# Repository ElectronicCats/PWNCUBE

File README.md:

# PWNCUBE - The Vulnerable Satellite Hacking Platform for Learning Through Research

PwnSat is the first open-source, vulnerable-by-design aerospace cybersecurity platform. It bridges the gap between traditional IT security and specialized Space Mission Operations (SMO). Developed over six years of research, PwnSat 2.0 scales from a basic FlatSat to a high-fidelity enterprise environment, designed specifically for advanced offensive and defensive research.

## Project Overview

PwnSat replicates a complete end-to-end space mission ecosystem, allowing researchers to explore vulnerabilities across the entire attack surface:
* **Space Segment:** 1U CubeSat Hardware (OBC, EPS, and Radio).
* **Ground Segment:** Multi-band RF Gateway (LoRa/FSK).
* **C3 Segment:** Native integration with Ball Aerospace COSMOS for enterprise-grade command and control.

## New for v2.0 (Black Hat USA Release)

The 2.0 "Enterprise Edition" introduces critical updates over the initial release:
* **GNSS Attack Module:** Integration of a physical GNSS sensor to simulate signal jamming and positioning spoofing, affecting the satellite's AOCS (Attitude and Orbit Control System).
* **COSMOS C3 Integration:** Support for industry-standard mission control software, replacing custom dashboards with tools used by NASA and commercial space ventures.
* **Ground Station Pivot:** New scenarios demonstrating lateral movement from a compromised MOC backend to the satellite RF uplink.

## Hardware Architecture

The platform is built on custom-designed PCBs (v1.1) optimized for RF integrity and modularity.

### Flight System Components

| Component | Specification |
| :--- | :--- |
| **OBC (Flight Computer)** | ESP32-S3 (Dual-core, hardware encryption support) |
| **Radio Subsystem** | Semtech SX1276/78 (Multi-band LoRa/FSK) |
| **GNSS Module** | Integrated positioning sensor for navigation research |
| **Sensors** | IMU, Thermal, and Simulated Power System (EPS) |

### Hardware Gallery

The following boards represent the core of the PwnSat 1U system:

**1. Main Flight Computer (OBC) & Navigation Board**
This board handles the flight logic, telemetry processing, and the newly integrated GNSS sensor.

**2. RF Communications & Shielding Subsystem**
Dedicated module for handling CCSDS and AX.25 protocol stacks over the physical radio link.

**3. Power Distribution & Modular Bus**
The EPS (Electronic Power System) simulation board, featuring intentional vulnerabilities in power rail management.

## Technical Research Scenarios (SPARTA Mapping)

Each vulnerability in PwnSat is mapped to the **SPARTA (Space Attack Research & Tactics Analysis)** framework to ensure professional-grade research relevance:

### 1. Electronic ASAT (Navigation Spoofing)
Using the new GNSS module, researchers can demonstrate how spoofing signal data tricks the OBC into incorrect positioning calculations, leading to unauthorized attitude maneuvers.

### 2. Space Link Exploitation
* **Uplink Hijacking:** Injecting unauthorized CCSDS frames into the command stream.
* **Telemetry Forgery:** Manipulating AX.25 packets to mask malicious activity on the satellite.

### 3. Ground Segment Lateral Movement
Demonstration of a "Full-Chain" compromise:
* Exploiting a web-based vulnerability in the MOC.
* Pivoting to the COSMOS C3 instance.
* Executing an unauthorized "Kill-Command" through the RF Ground Station.

## Repository Structure

* `/hardware`: KiCad schematics, Gerber files, and Bill of Materials (BOM).
* `/firmware`: ESP32-S3 flight code and radio drivers (PlatformIO).
* `/ground-station`: Dockerized MOC and Ball Aerospace COSMOS configuration files.
* `/docs`: Technical architecture whitepapers and SPARTA mapping guides.

## Disclaimer

PwnSat is intended for educational and ethical research purposes only. Always conduct RF testing within a shielded environment (Faraday cage) to comply with local radio frequency regulations.

## Credits & License

**Developed by:** PWNSAT Team & Electronic Cats
**Research Duration:** 2019 - 2026
**License:** GNU General Public License v3.0

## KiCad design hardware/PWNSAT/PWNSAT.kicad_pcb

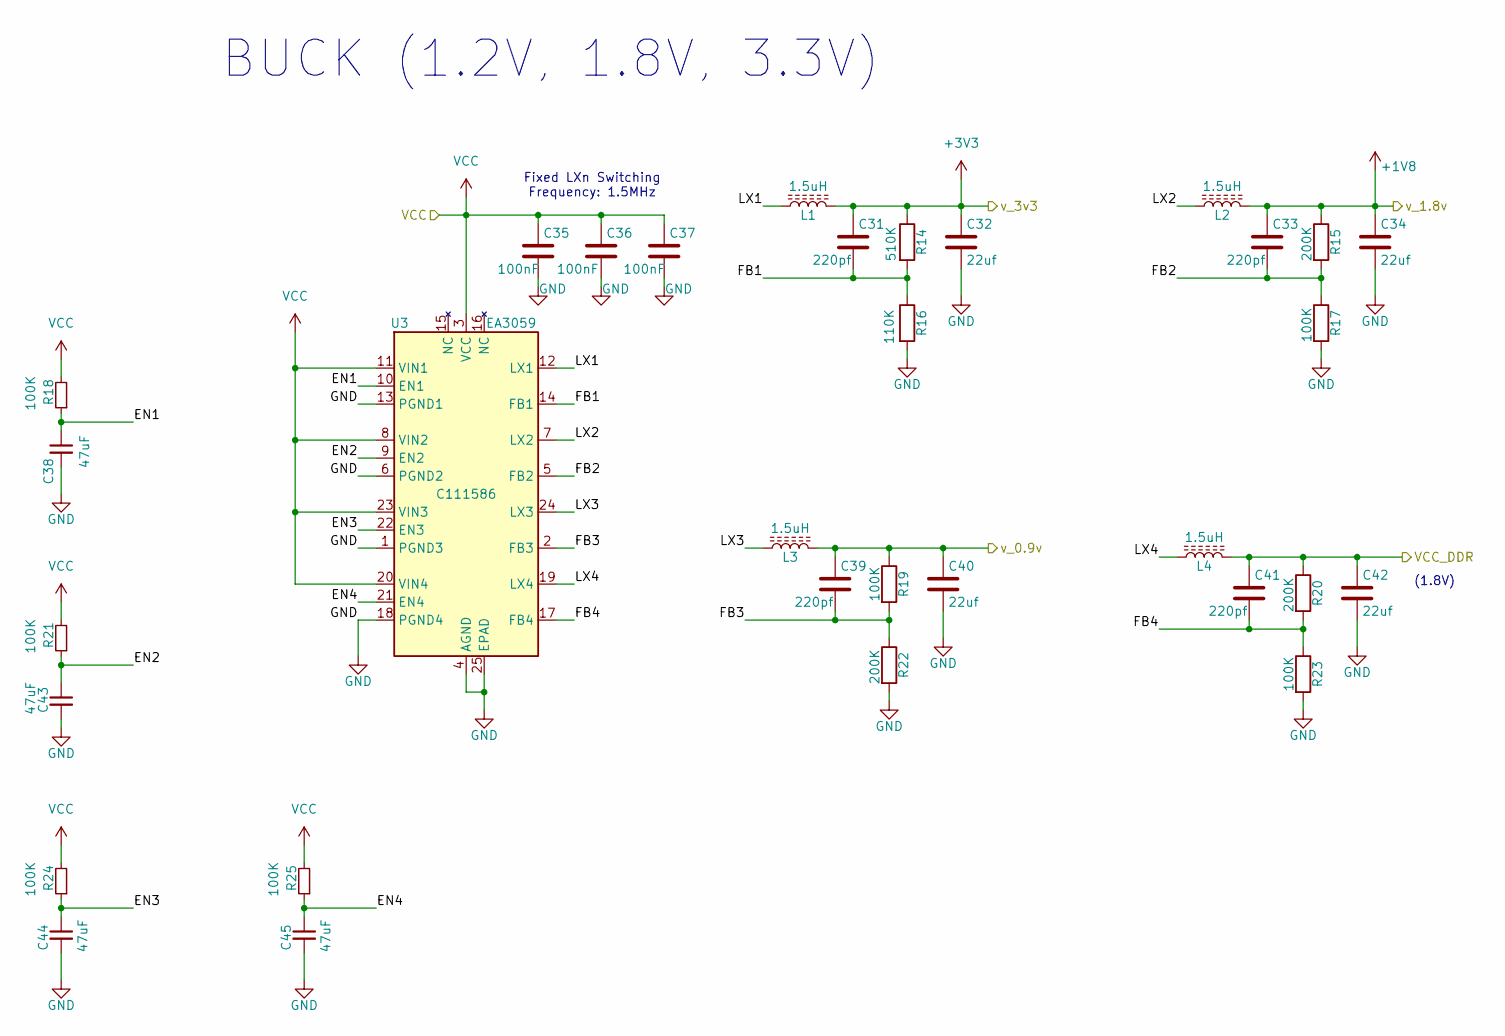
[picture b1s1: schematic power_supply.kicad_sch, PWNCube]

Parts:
C31, C33, C39, C41: 220pf; C_0402_1005Metric_Pad0.74x0.62mm_HandSolder; LCSC# C327000
C32, C34, C40, C42: 22uf; C_0402_1005Metric_Pad0.74x0.62mm_HandSolder; LCSC# C415703
C35, C36, C37: 100nF; C_0402_1005Metric_Pad0.74x0.62mm_HandSolder; LCSC# C77020
C38, C43, C44, C45: 47uF; C_0603_1608Metric; LCSC# C140782
L1, L2, L3, L4: 1.5uH; L_1008_2520Metric; LCSC# C7427193
R14: 510K; R_0402_1005Metric_Pad0.72x0.64mm_HandSolder; LCSC# C365024
R15, R20, R22: 200K; R_0402_1005Metric_Pad0.72x0.64mm_HandSolder; LCSC# C364966
R16: 110K; R_0402_1005Metric_Pad0.72x0.64mm_HandSolder
R17, R18, R19, R21, R23, R24, R25: 100K; R_0402_1005Metric_Pad0.72x0.64mm_HandSolder; LCSC# C844674
U3: EA3059; VQFN-24-1EP_4x4mm_P0.5mm_EP2.5x2.5mm; LCSC# C111586

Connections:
+1V8: C33.1, C34.1, L2.2, R15.1; also elsewhere on the board
+3V3: C31.1, C32.1, L1.2, R14.1; also elsewhere on the board
/core/VCC_DDR: C41.1, C42.1, L4.2, R20.1; also elsewhere on the board
/core/VDD_ARM: C39.1, C40.1, L3.2, R19.1; also elsewhere on the board
/power_supply/EN1: C38.1, R18.1, U3.10 (EN1)
/power_supply/EN2: C43.1, R21.1, U3.9 (EN2)
/power_supply/EN3: C44.1, R24.1, U3.22 (EN3)
/power_supply/EN4: C45.1, R25.1, U3.21 (EN4)
/power_supply/FB1: C31.2, R14.2, R16.1, U3.14 (FB1)
/power_supply/FB2: C33.2, R15.2, R17.1, U3.5 (FB2)
/power_supply/FB3: C39.2, R19.2, R22.1, U3.2 (FB3)
/power_supply/FB4: C41.2, R20.2, R23.1, U3.17 (FB4)
/power_supply/LX1: L1.1, U3.12 (LX1)
/power_supply/LX2: L2.1, U3.7 (LX2)
/power_supply/LX3: L3.1, U3.24 (LX3)
/power_supply/LX4: L4.1, U3.19 (LX4)
GND: C32.2, C34.2, C35.2, C36.2, C37.2, C38.2, C40.2, C42.2, C43.2, C44.2, C45.2, R16.2, R17.2, R22.2, R23.2, U3.1 (PGND3), U3.4 (AGND), U3.6 (PGND2), U3.13 (PGND1), U3.18 (PGND4), U3.25 (EPAD); also elsewhere on the board
VCC: C35.1, C36.1, C37.1, R18.2, R21.2, R24.2, R25.2, U3.3 (VCC), U3.8 (VIN2), U3.11 (VIN1), U3.20 (VIN4), U3.23 (VIN3); also elsewhere on the board

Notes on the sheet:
BUCK (1.2V, 1.8V, 3.3V)
Fixed LXn Switching Frequency: 1.5MHz
(1.8V)

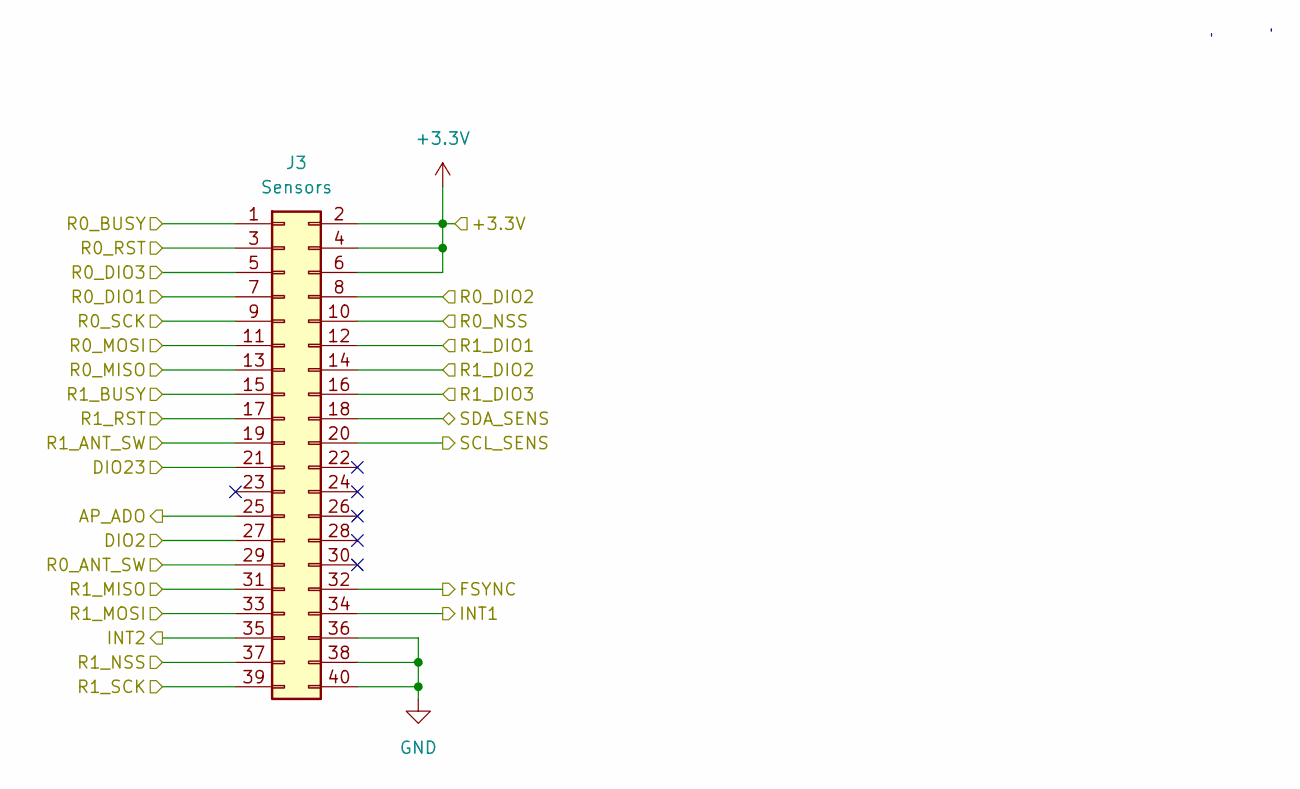
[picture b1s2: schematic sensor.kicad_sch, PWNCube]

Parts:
J3: Sensors; PinHeader_2x20_P2.54mm_Vertical

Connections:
+3.3V: J3.2, J3.4, J3.6; also elsewhere on the board
/Sensor/AP_ADO: J3.25; also elsewhere on the board
/Sensor/DIO2: J3.27; also elsewhere on the board
/Sensor/DIO23: J3.21; also elsewhere on the board
/Sensor/FSYNC: J3.32; also elsewhere on the board
/Sensor/INT1: J3.34; also elsewhere on the board
/Sensor/INT2: J3.35; also elsewhere on the board
/Sensor/R0_ANT_SW: J3.29; also elsewhere on the board
/Sensor/R0_BUSY: J3.1; also elsewhere on the board
/Sensor/R0_DIO1: J3.7; also elsewhere on the board
/Sensor/R0_DIO2: J3.8; also elsewhere on the board
/Sensor/R0_DIO3: J3.5; also elsewhere on the board
/Sensor/R0_MISO: J3.13; also elsewhere on the board
/Sensor/R0_MOSI: J3.11; also elsewhere on the board
/Sensor/R0_NSS: J3.10; also elsewhere on the board
/Sensor/R0_RST: J3.3; also elsewhere on the board
/Sensor/R0_SCK: J3.9; also elsewhere on the board
/Sensor/R1_ANT_SW: J3.19; also elsewhere on the board
/Sensor/R1_BUSY: J3.15; also elsewhere on the board
/Sensor/R1_DIO1: J3.12; also elsewhere on the board
/Sensor/R1_DIO2: J3.14; also elsewhere on the board
/Sensor/R1_DIO3: J3.16; also elsewhere on the board
/Sensor/R1_MISO: J3.31; also elsewhere on the board
/Sensor/R1_MOSI: J3.33; also elsewhere on the board
/Sensor/R1_NSS: J3.37; also elsewhere on the board
/Sensor/R1_RST: J3.17; also elsewhere on the board
/Sensor/R1_SCK: J3.39; also elsewhere on the board
/Sensor/SCL_SENS: J3.20; also elsewhere on the board
/Sensor/SDA_SENS: J3.18; also elsewhere on the board
GND: J3.36, J3.38, J3.40; also elsewhere on the board

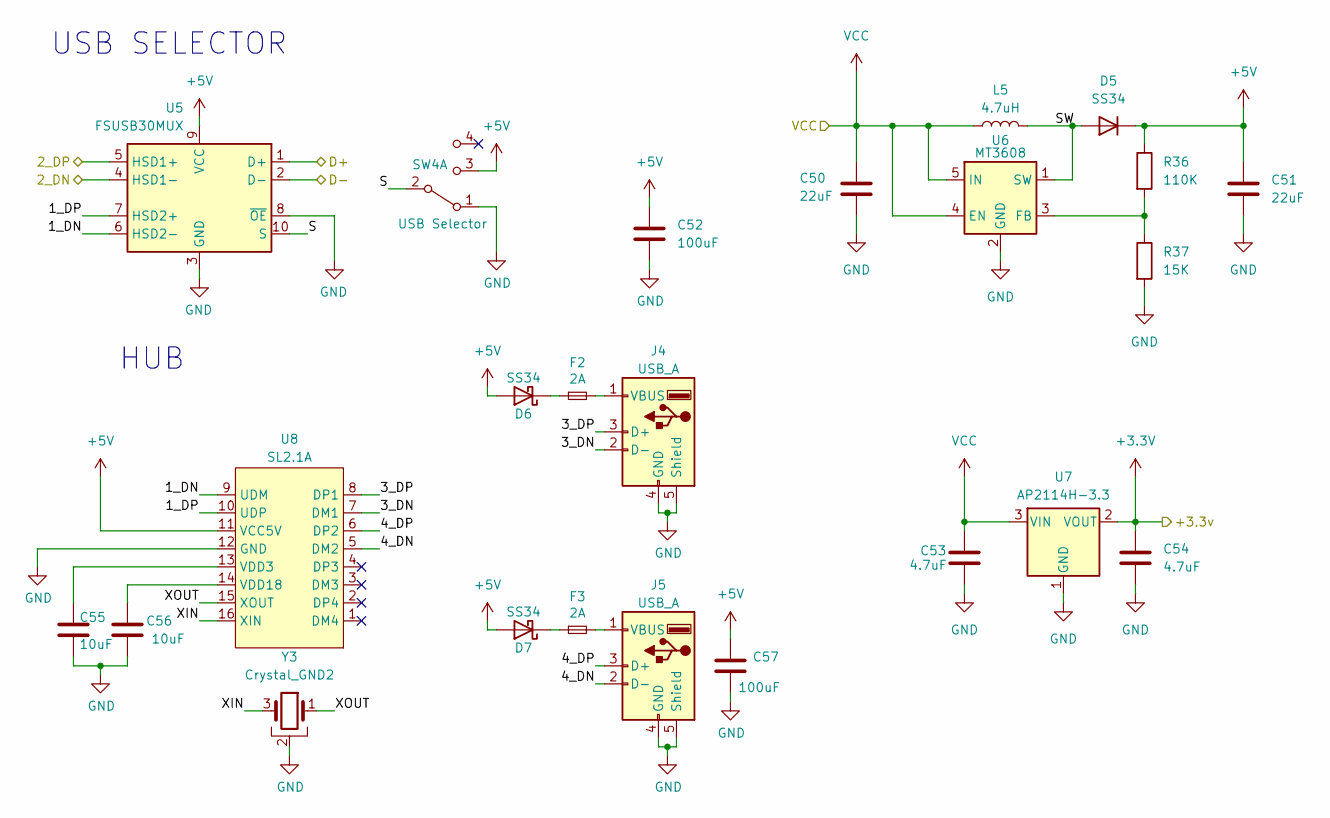
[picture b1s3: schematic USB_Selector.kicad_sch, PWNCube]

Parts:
C50, C51: 22uF; C_0402_1005Metric; LCSC# C415703
C52, C57: 100uF; C_0805_2012Metric; LCSC# C141660
C53, C54: 4.7uF; C_0402_1005Metric; LCSC# C368809
C55, C56: 10uF; C_0603_1608Metric; LCSC# C96446
D5, D6, D7: SS34; D_SMA; LCSC# C908680
F2, F3: 2A; Fuse_0603_1608Metric; LCSC# C41380229
J4, J5: USB_A; USB_A_Connfly_DS1095; LCSC# C2345
L5: 4.7uH; LQH5BPN; LCSC# C520334
R36: 110K; R_0603_1608Metric; LCSC# C326736
R37: 15K; R_0603_1608Metric; LCSC# C2989599
SW4: USB Selector; SW_Slide_SPDT_Angled_CK_OS102011MA1Q; LCSC# C393937
U5: FSUSB30MUX; IC_FSUSB42UMX; LCSC# C42370490
U6: MT3608; SOT-23-6; LCSC# C2932326
U7: AP2114H-3.3; SOT-223-3_TabPin2; LCSC# C150716
U8: SL2.1A; SO-16_3.9x9.9mm_P1.27mm; LCSC# C192893
Y3: Crystal_GND2; Crystal_SMD_3225-4Pin_3.2x2.5mm; LCSC# C133334

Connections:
+3.3V: C54.1, U7.2 (VOUT); also elsewhere on the board
+5V: C51.1, C52.1, C57.1, D5.1 (K), D6.2 (A), D7.2 (A), R36.1, SW4.3 (C), U5.9 (VCC), U8.11 (VCC5V)
/Source_Connector/2_DN: U5.4 (HSD1-); also elsewhere on the board
/Source_Connector/2_DP: U5.5 (HSD1+); also elsewhere on the board
/USB_Selector/1_DN: U5.6 (HSD2-), U8.9 (UDM)
/USB_Selector/1_DP: U5.7 (HSD2+), U8.10 (UDP)
/USB_Selector/3_DN: J4.2 (D-), U8.7 (DM1)
/USB_Selector/3_DP: J4.3 (D+), U8.8 (DP1)
/USB_Selector/4_DN: J5.2 (D-), U8.5 (DM2)
/USB_Selector/4_DP: J5.3 (D+), U8.6 (DP2)
/USB_Selector/D+: U5.1 (D+); also elsewhere on the board
/USB_Selector/D-: U5.2 (D-); also elsewhere on the board
/USB_Selector/S: SW4.2 (B), U5.10 (S)
/USB_Selector/SW: D5.2 (A), L5.2, U6.1 (SW)
/USB_Selector/XIN: U8.16 (XIN), Y3.3
/USB_Selector/XOUT: U8.15 (XOUT), Y3.1
GND: C50.2, C51.2, C52.2, C53.2, C54.2, C55.2, C56.1, C57.2, J4.4 (GND), J4.5 (Shield), J5.4 (GND), J5.5 (Shield), R37.2, SW4.1 (A), U5.3 (GND), U5.8 (~OE), U6.2 (GND), U7.1 (GND), U8.12 (GND), Y3.2, Y3.4; also elsewhere on the board
unnamed: D6.1 (K), F2.1
unnamed: D7.1 (K), F3.1
unnamed: F2.2, J4.1 (VBUS)
unnamed: F3.2, J5.1 (VBUS)
unnamed: R36.2, R37.1, U6.3 (FB)
unnamed: C55.1, U8.13 (VDD3)
unnamed: C56.2, U8.14 (VDD18)
VCC: C50.1, C53.1, L5.1, U6.4 (EN), U6.5 (IN), U7.3 (VIN); also elsewhere on the board

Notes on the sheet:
HUB
USB SELECTOR

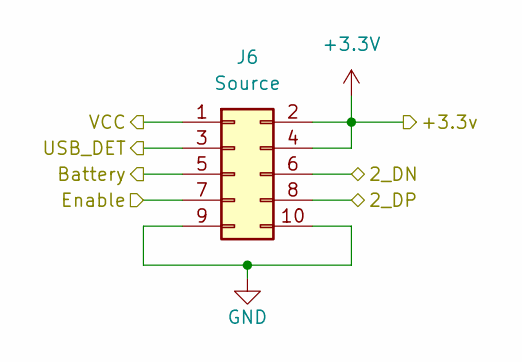
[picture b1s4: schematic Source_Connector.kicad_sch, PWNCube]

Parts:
J6: Source; PinHeader_2x05_P2.54mm_Vertical; LCSC# C7501191

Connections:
+3.3V: J6.2, J6.4; also elsewhere on the board
/Source_Connector/2_DN: J6.6; also elsewhere on the board
/Source_Connector/2_DP: J6.8; also elsewhere on the board
/Source_Connector/Battery: J6.5; also elsewhere on the board
/Source_Connector/Enable: J6.7; also elsewhere on the board
/Source_Connector/USB_DET: J6.3; also elsewhere on the board
GND: J6.9, J6.10; also elsewhere on the board
VCC: J6.1; also elsewhere on the board

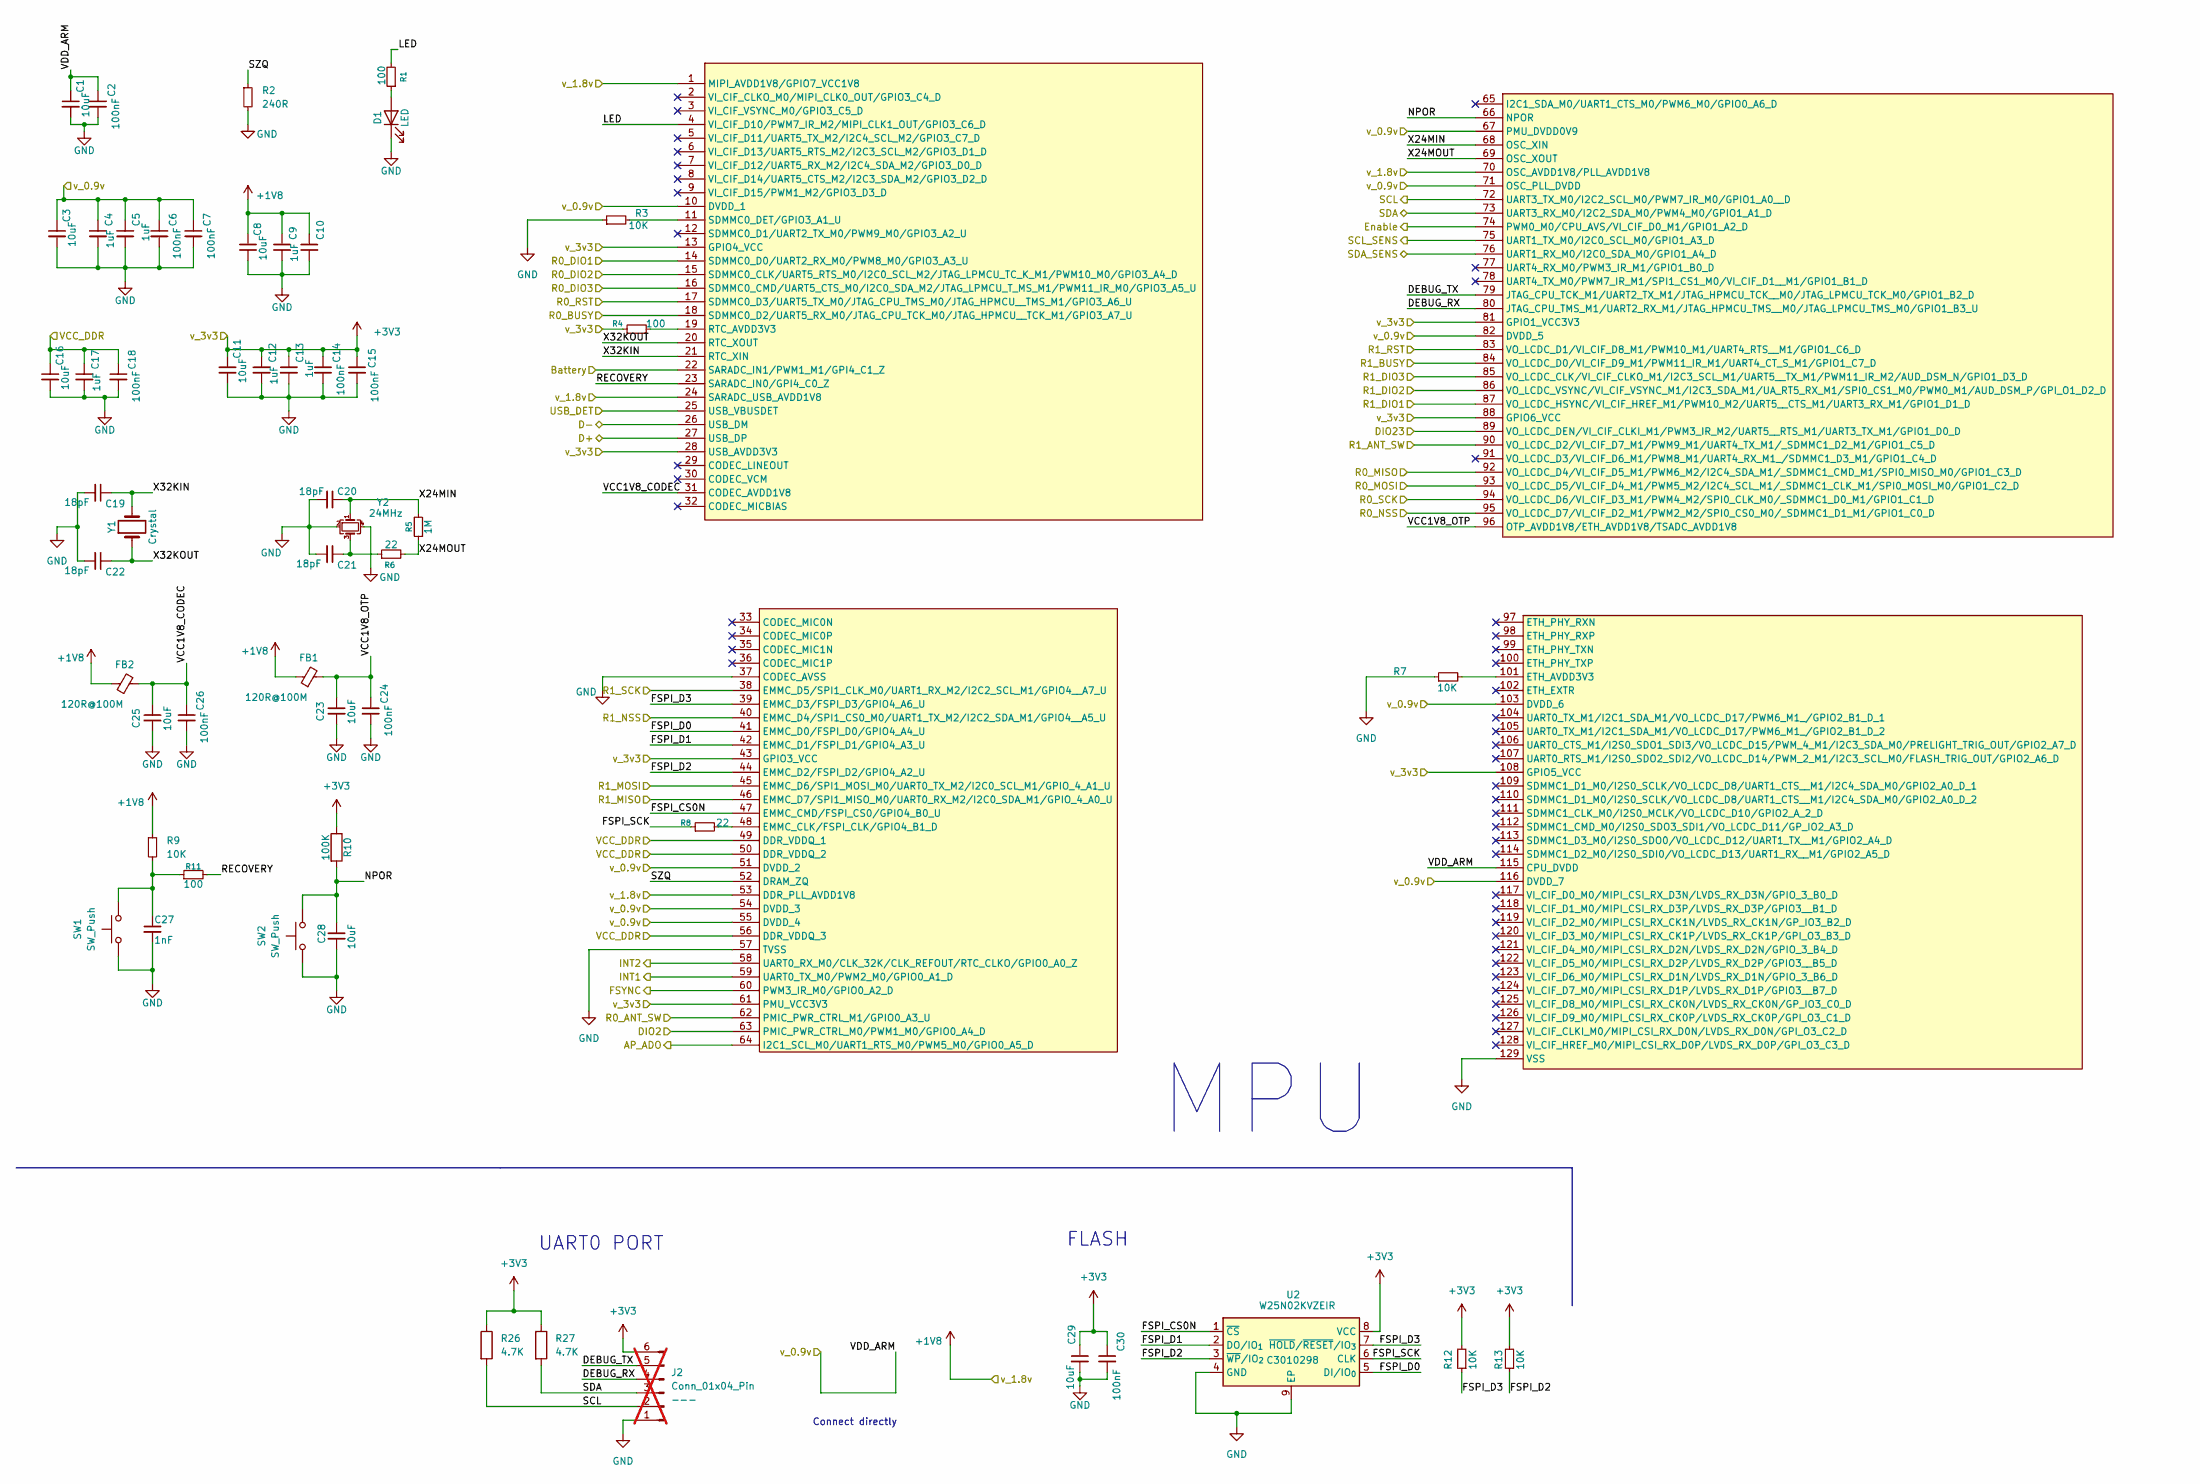
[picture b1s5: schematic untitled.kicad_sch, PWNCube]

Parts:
C1, C3, C8, C11, C16, C23, C25, C28, C29: 10uF; C_0603_1608Metric; LCSC# C96446
C2, C6, C7, C14, C15, C18, C24, C26, C30: 100nF; C_0402_1005Metric_Pad0.74x0.62mm_HandSolder; LCSC# C77020
C4, C5, C9, C10, C12, C13, C17: 1uF; C_0402_1005Metric_Pad0.74x0.62mm_HandSolder; LCSC# C52923
C19, C20, C21, C22: 18pF; C_0402_1005Metric_Pad0.74x0.62mm_HandSolder; LCSC# C161534
C27: 1nF; C_0402_1005Metric_Pad0.74x0.62mm_HandSolder; LCSC# C189467
D1: LED; LED_0603_1608Metric; LCSC# C375573
FB1, FB2: 120R@100M; L_0603_1608Metric; LCSC# C14709
J2: Conn_01x04_Pin; PinHeader_1x06_P2.54mm_Vertical; LCSC# ---; not fitted
R1, R4, R11: 100; R_0603_1608Metric; LCSC# C253328
R2: 240R; R_0402_1005Metric_Pad0.72x0.64mm_HandSolder
R3, R7, R9, R12, R13: 10K; R_0402_1005Metric_Pad0.72x0.64mm_HandSolder; LCSC# C2759535
R5: 1M; R_0402_1005Metric_Pad0.72x0.64mm_HandSolder; LCSC# C131492
R6, R8: 22; R_0603_1608Metric
R10: 100K; R_0402_1005Metric_Pad0.72x0.64mm_HandSolder; LCSC# C844674
R26, R27: 4.7K; R_0402_1005Metric_Pad0.72x0.64mm_HandSolder; LCSC# C400631
SW1, SW2: SW_Push; TS1088R02026; LCSC# C455281
U1: RV1106G3; LCSC# C5328706
U2: W25N02KVZEIR; WSON-8-1EP_8x6mm_P1.27mm_EP3.4x4.3mm; LCSC# C3010298
Y1: Crystal; Crystal_SMD_3215-2Pin_3.2x1.5mm; LCSC# C620155
Y2: 24MHz; Crystal_SMD_3225-4Pin_3.2x2.5mm; LCSC# C70590

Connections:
+1V8: C8.1, C9.1, C10.1, FB1.1, FB2.1, R9.1, U1.1 (MIPI_AVDD1V8/GPIO7_VCC1V8), U1.24 (SARADC_USB_AVDD1V8), U1.53 (DDR_PLL_AVDD1V8), U1.70 (OSC_AVDD1V8/PLL_AVDD1V8); also elsewhere on the board
+3V3: C11.1, C12.1, C13.1, C14.1, C15.1, C29.1, C30.1, J2.6, R4.1, R10.1, R12.2, R13.2, R26.1, R27.1, U1.13 (GPIO4_VCC), U1.28 (USB_AVDD3V3), U1.43 (GPIO3_VCC), U1.61 (PMU_VCC3V3), U1.81 (GPIO1_VCC3V3), U1.88 (GPIO6_VCC), U1.108 (GPIO5_VCC), U2.8 (VCC); also elsewhere on the board
/Sensor/AP_ADO: U1.64 (I2C1_SCL_M0/UART1_RTS_M0/PWM5_M0/GPIO0_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); also elsewhere on the board
/Sensor/DIO2: U1.63 (PMIC_PWR_CTRL_M0/PWM1_M0/GPIO0_A4_D); also elsewhere on the board
/Sensor/DIO23: U1.89 (VO_LCDC_DEN/VI_CIF_CLKI_M1/PWM3_IR_M2/U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); also elsewhere on the board
/Sensor/FSYNC: U1.60 (PWM3_IR_M0/GPIO0_A2_D); also elsewhere on the board
/Sensor/INT1: U1.59 (UART0_TX_M0/PWM2_M0/GPIO0_A1_D); also elsewhere on the board
/Sensor/INT2: U1.58 (UART0_RX_M0/CLK_32K/CLK_REFOUT/RTC_CLKO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); also elsewhere on the board
/Sensor/R0_ANT_SW: U1.62 (PMIC_PWR_CTRL_M1/GPIO0_A3_U); also elsewhere on the board
/Sensor/R0_BUSY: U1.18 (SDMMC0_D2/UART5_RX_M0/JTAG_CPU_TCK_M0/J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); also elsewhere on the board
/Sensor/R0_DIO1: U1.14 (SDMMC0_D0/UART2_RX_M0/PWM8_M0/GPIO3_A3_U); also elsewhere on the board
/Sensor/R0_DIO2: U1.15 (SDMMC0_CLK/UART5_RTS_M0/I2C0_SCL_M2/JTA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); also elsewhere on the board
/Sensor/R0_DIO3: U1.16 (SDMMC0_CMD/UART5_CTS_M0/I2C0_SDA_M2/JTA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); also elsewhere on the board
/Sensor/R0_MISO: U1.92 (VO_LCDC_D4/VI_CIF_D5_M1/PWM6_M2/I2C4_SD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); also elsewhere on the board
/Sensor/R0_MOSI: U1.93 (VO_LCDC_D5/VI_CIF_D4_M1/PWM5_M2/I2C4_SC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); also elsewhere on the board
/Sensor/R0_NSS: U1.95 (VO_LCDC_D7/VI_CIF_D2_M1/PWM2_M2/SPI0_CS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); also elsewhere on the board
/Sensor/R0_RST: U1.17 (SDMMC0_D3/UART5_TX_M0/JTAG_CPU_TMS_M0/J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); also elsewhere on the board
/Sensor/R0_SCK: U1.94 (VO_LCDC_D6/VI_CIF_D3_M1/PWM4_M2/SPI0_CL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); also elsewhere on the board
/Sensor/R1_ANT_SW: U1.90 (VO_LCDC_D2/VI_CIF_D7_M1/PWM9_M1/UART4_T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); also elsewhere on the board
/Sensor/R1_BUSY: U1.84 (VO_LCDC_D0/VI_CIF_D9_M1/PWM11_IR_M1/UAR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); also elsewhere on the board
/Sensor/R1_DIO1: U1.87 (VO_LCDC_HSYNC/VI_CIF_HREF_M1/PWM10_M2/U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); also elsewhere on the board
/Sensor/R1_DIO2: U1.86 (VO_LCDC_VSYNC/VI_CIF_VSYNC_M1/I2C3_SDA_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); also elsewhere on the board
/Sensor/R1_DIO3: U1.85 (VO_LCDC_CLK/VI_CIF_CLKO_M1/I2C3_SCL_M1/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); also elsewhere on the board
/Sensor/R1_MISO: U1.46 (EMMC_D7/SPI1_MISO_M0/UART0_RX_M2/I2C0_S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); also elsewhere on the board
/Sensor/R1_MOSI: U1.45 (EMMC_D6/SPI1_MOSI_M0/UART0_TX_M2/I2C0_S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); also elsewhere on the board
/Sensor/R1_NSS: U1.40 (EMMC_D4/SPI1_CS0_M0/UART1_TX_M2/I2C2_SD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); also elsewhere on the board
/Sensor/R1_RST: U1.83 (VO_LCDC_D1/VI_CIF_D8_M1/PWM10_M1/UART4_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); also elsewhere on the board
/Sensor/R1_SCK: U1.38 (EMMC_D5/SPI1_CLK_M0/UART1_RX_M2/I2C2_SC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); also elsewhere on the board
/Sensor/SCL_SENS: U1.75 (UART1_TX_M0/I2C0_SCL_M0/GPIO1_A3_D); also elsewhere on the board
/Sensor/SDA_SENS: U1.76 (UART1_RX_M0/I2C0_SDA_M0/GPIO1_A4_D); also elsewhere on the board
/Source_Connector/Battery: U1.22 (SARADC_IN1/PWM1_M1/GPI4_C1_Z); also elsewhere on the board
/Source_Connector/Enable: U1.74 (PWM0_M0/CPU_AVS/VI_CIF_D0_M1/GPIO1_A2_D); also elsewhere on the board
/Source_Connector/USB_DET: U1.25 (USB_VBUSDET); also elsewhere on the board
/USB_Selector/D+: U1.27 (USB_DP); also elsewhere on the board
/USB_Selector/D-: U1.26 (USB_DM); also elsewhere on the board
/core/DEBUG_RX: J2.4, U1.80 (JTAG_CPU_TMS_M1/UART2_RX_M1/JTAG_HPMCU_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)
/core/DEBUG_TX: J2.5, U1.79 (JTAG_CPU_TCK_M1/UART2_TX_M1/JTAG_HPMCU_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)
/core/FSPI_CS0N: U1.47 (EMMC_CMD/FSPI_CS0/GPIO4_B0_U), U2.1 (~CS)
/core/FSPI_D0: U1.41 (EMMC_D0/FSPI_D0/GPIO4_A4_U), U2.5 (DI/IO_{0})
/core/FSPI_D1: U1.42 (EMMC_D1/FSPI_D1/GPIO4_A3_U), U2.2 (DO/IO_{1})
/core/FSPI_D2: R13.1, U1.44 (EMMC_D2/FSPI_D2/GPIO4_A2_U), U2.3 (~WP/IO_{2})
/core/FSPI_D3: R12.1, U1.39 (EMMC_D3/FSPI_D3/GPIO4_A6_U), U2.7 (~HOLD/~RESET/IO_{3})
/core/FSPI_SCK: R8.1, U2.6 (CLK)
/core/LED: R1.2, U1.4 (VI_CIF_D10/PWM7_IR_M2/MIPI_CLK1_OUT/GPI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)
/core/NPOR: C28.1, R10.2, SW2.2, U1.66 (NPOR)
/core/RECOVERY: R11.2, U1.23 (SARADC_IN0/GPI4_C0_Z)
/core/SCL: J2.2, R26.2, U1.72 (UART3_TX_M0/I2C2_SCL_M0/PWM7_IR_M0/GPIO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)
/core/SDA: J2.3, R27.2, U1.73 (UART3_RX_M0/I2C2_SDA_M0/PWM4_M0/GPIO1_A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)
/core/SZQ: R2.1, U1.52 (DRAM_ZQ)
/core/VCC1V8_CODEC: C25.1, C26.1, FB2.2, U1.31 (CODEC_AVDD1V8)
/core/VCC1V8_OTP: C23.1, C24.1, FB1.2, U1.96 (OTP_AVDD1V8/ETH_AVDD1V8/TSADC_AVDD1V8)
/core/VCC_DDR: C16.1, C17.1, C18.1, U1.49 (DDR_VDDQ_1), U1.50 (DDR_VDDQ_2), U1.56 (DDR_VDDQ_3); also elsewhere on the board
/core/VDD_ARM: C1.1, C2.1, C3.1, C4.1, C5.1, C6.1, C7.1, U1.10 (DVDD_1), U1.51 (DVDD_2), U1.54 (DVDD_3), U1.55 (DVDD_4), U1.67 (PMU_DVDD0V9), U1.71 (OSC_PLL_DVDD), U1.82 (DVDD_5), U1.103 (DVDD_6), U1.115 (CPU_DVDD), U1.116 (DVDD_7); also elsewhere on the board
/core/X24MIN: C20.1, R5.1, U1.68 (OSC_XIN), Y2.1
/core/X24MOUT: R5.2, R6.2, U1.69 (OSC_XOUT)
/core/X32KIN: C19.1, U1.21 (RTC_XIN), Y1.2
/core/X32KOUT: C22.1, U1.20 (RTC_XOUT), Y1.1
GND: C1.2, C2.2, C3.2, C4.2, C5.2, C6.2, C7.2, C8.2, C9.2, C10.2, C11.2, C12.2, C13.2, C14.2, C15.2, C16.2, C17.2, C18.2, C19.2, C20.2, C21.2, C22.2, C23.2, C24.2, C25.2, C26.2, C27.2, C28.2, C29.2, C30.2, D1.1 (K), J2.1, R2.2, R3.1, R7.1, SW1.1, SW2.1, U1.37 (CODEC_AVSS), U1.57 (TVSS), U1.129 (VSS), U2.4 (GND), U2.9 (EP), Y2.2, Y2.4; also elsewhere on the board
unnamed: C21.1, R6.1, Y2.3
unnamed: C27.1, R9.2, R11.1, SW1.2
unnamed: D1.2 (A), R1.1
unnamed: R4.2, U1.19 (RTC_AVDD3V3)
unnamed: R3.2, U1.11 (SDMMC0_DET/GPIO3_A1_U)
unnamed: R8.2, U1.48 (EMMC_CLK/FSPI_CLK/GPIO4_B1_D)
unnamed: R7.2, U1.101 (ETH_AVDD3V3)

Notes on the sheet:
FLASH
UART0 PORT
MPU
Connect directly

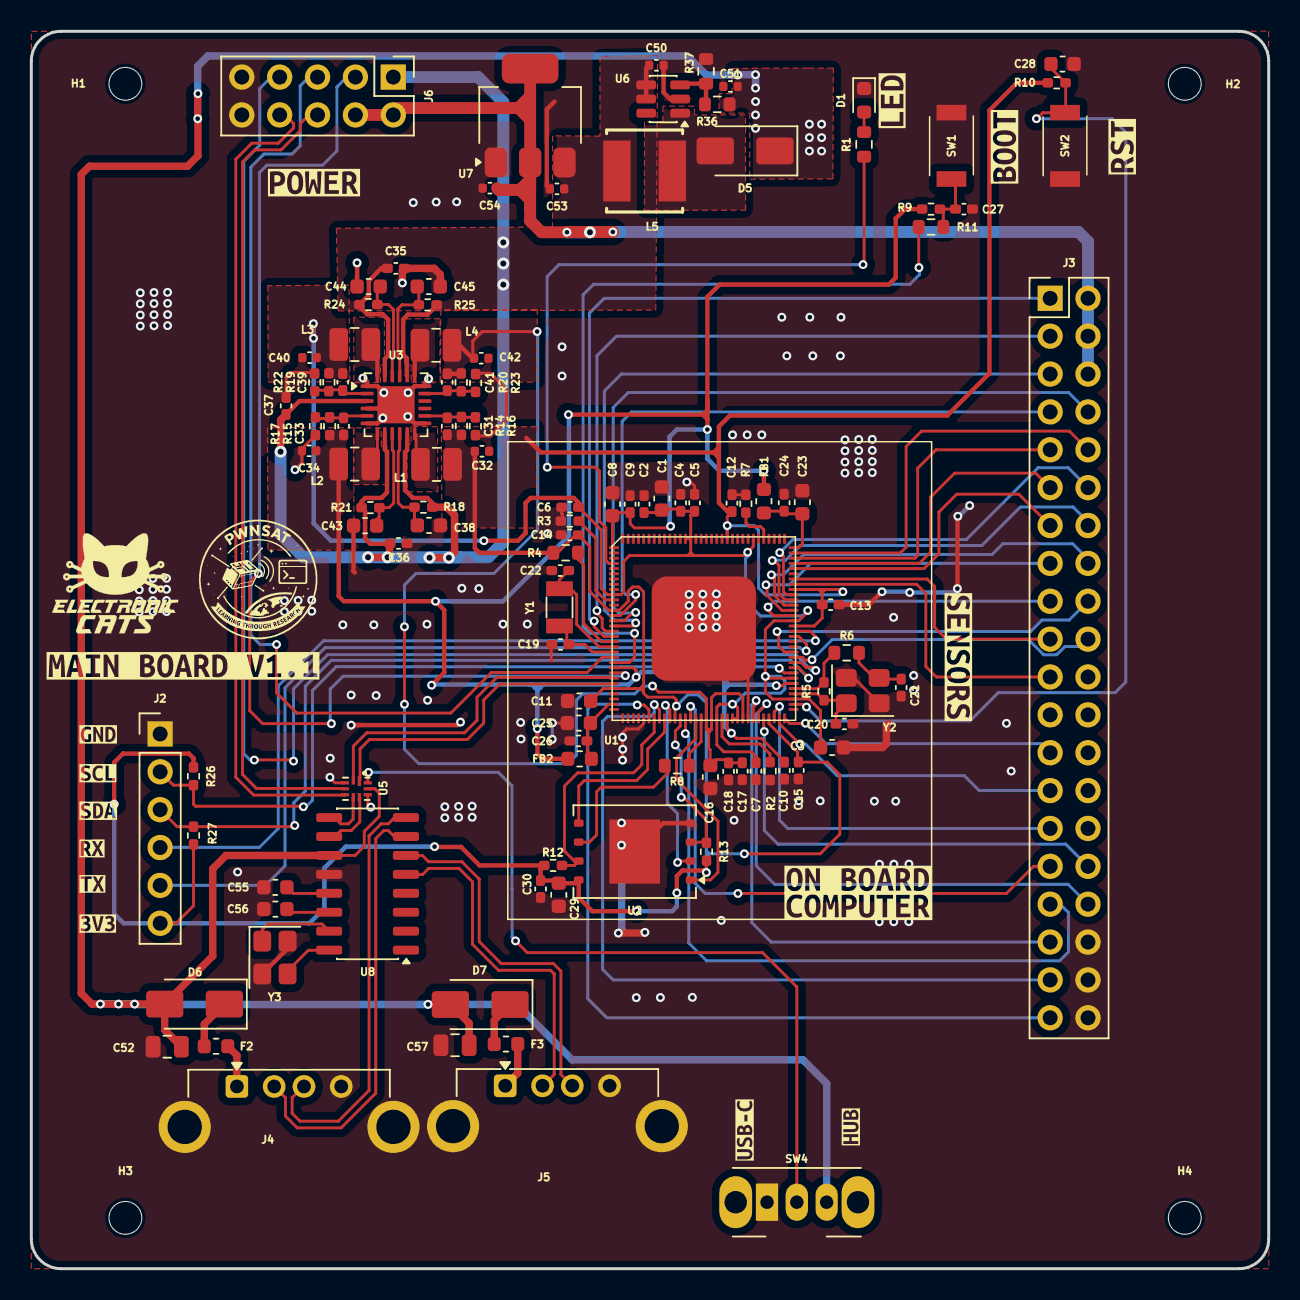
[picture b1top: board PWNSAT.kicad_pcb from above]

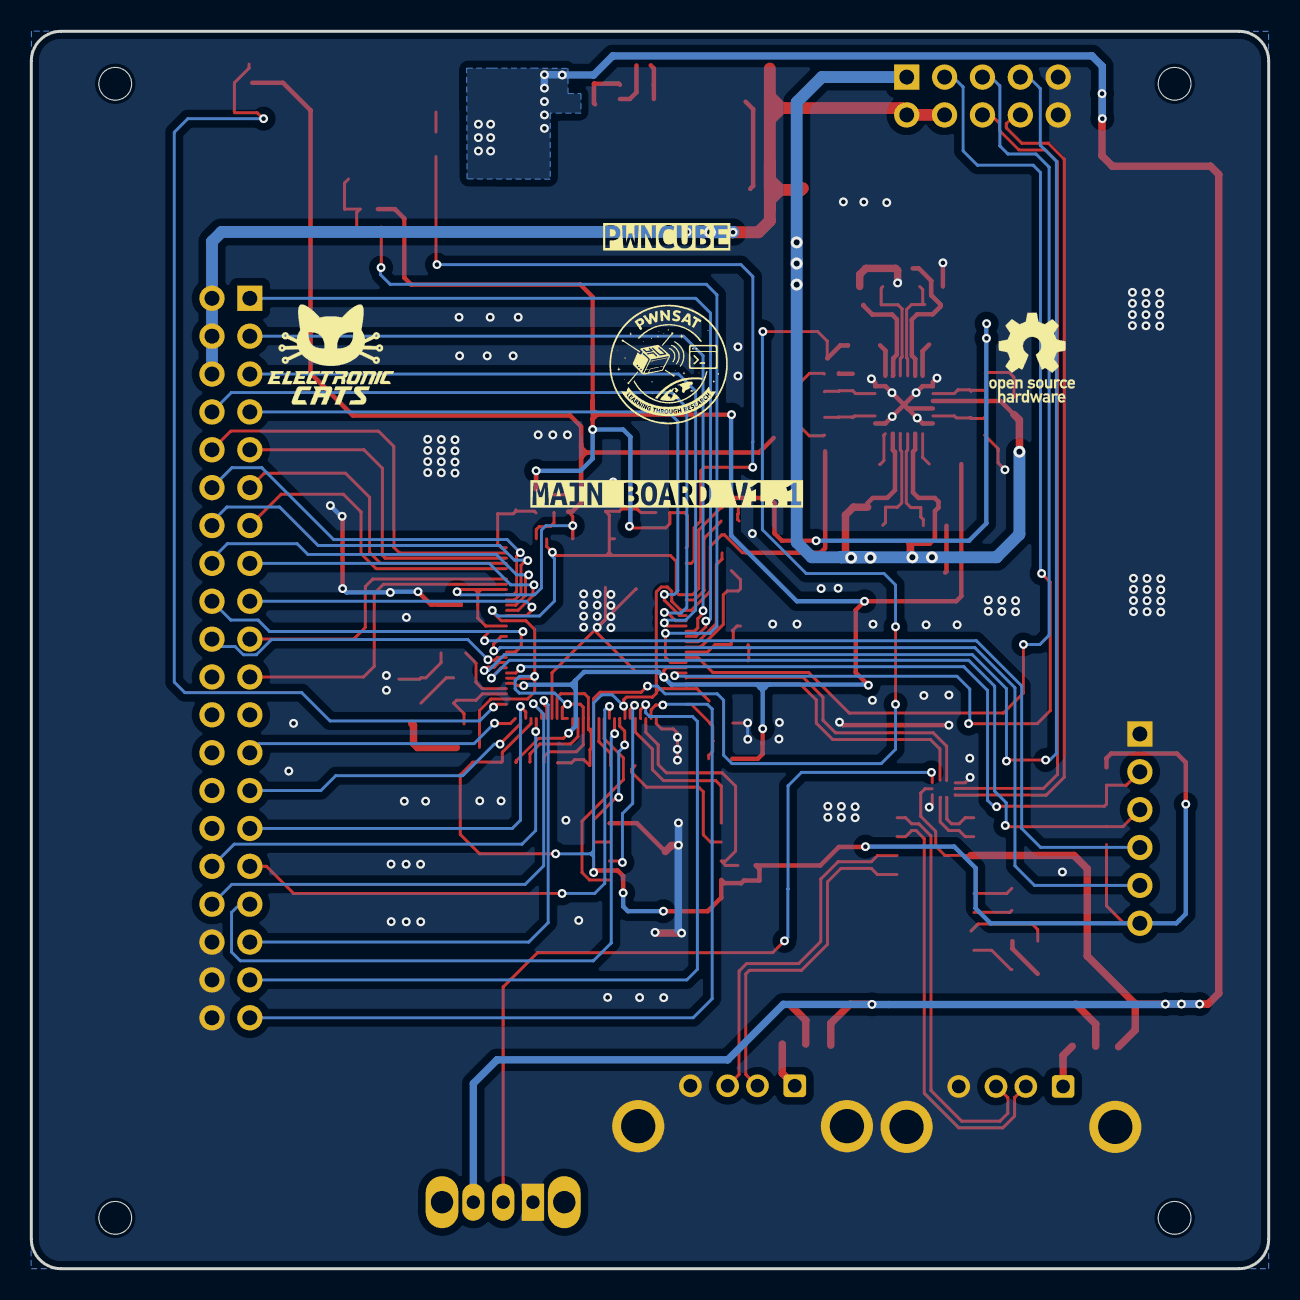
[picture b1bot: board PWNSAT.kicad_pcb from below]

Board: 2 copper layers, 83.0 x 83.0 mm, 135 parts (2 on the bottom side), 99 nets.

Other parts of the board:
H1, H2, H3, H4: MountingHole; MountingHole_2.2mm_M2
kibuzzard-69B43A9C: G***; kibuzzard-69B43A9C
kibuzzard-69B43B5E: G***; kibuzzard-69B43B5E
kibuzzard-6989FAE0: G***; kibuzzard-6989FAE0
kibuzzard-6989FAEE: G***; kibuzzard-6989FAEE
kibuzzard-698516AC: G***; kibuzzard-698516AC
kibuzzard-698516D4: G***; kibuzzard-698516D4
kibuzzard-698516F5: G***; kibuzzard-698516F5
kibuzzard-698517BF: G***; kibuzzard-698517BF
kibuzzard-698517CD: G***; kibuzzard-698517CD
kibuzzard-698517E4: G***; kibuzzard-698517E4
kibuzzard-698517F0: G***; kibuzzard-698517F0
kibuzzard-698615E5: G***; kibuzzard-698615E5
kibuzzard-6985157B: G***; kibuzzard-6985157B
kibuzzard-6985168F: G***; kibuzzard-6985168F
kibuzzard-6986164F: G***; kibuzzard-6986164F
kibuzzard-69851805: G***; kibuzzard-69851805
kibuzzard-69851812: G***; kibuzzard-69851812
kibuzzard-69861606: G***; kibuzzard-69861606

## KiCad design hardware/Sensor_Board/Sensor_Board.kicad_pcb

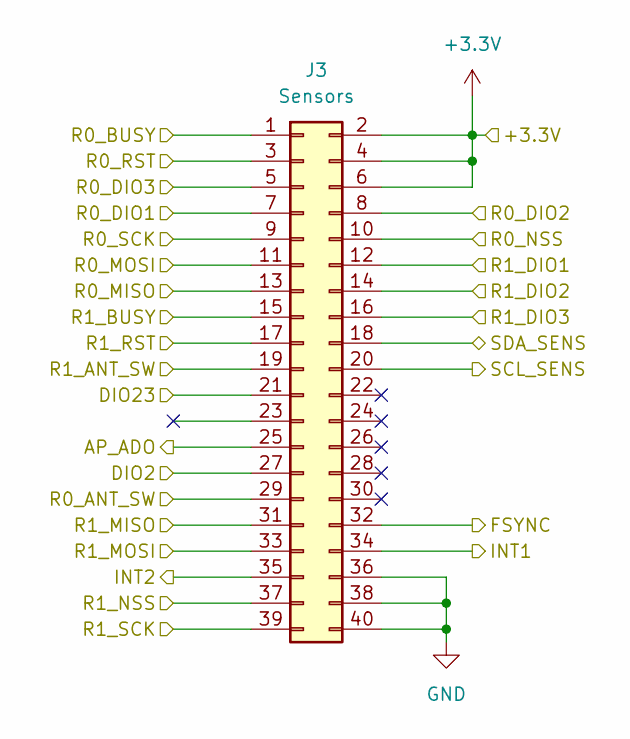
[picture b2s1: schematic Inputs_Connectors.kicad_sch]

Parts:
J3: Sensors; PinHeader_2x20_P2.54mm_Vertical

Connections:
+3.3V: J3.2, J3.4, J3.6; also elsewhere on the board
/Inputs_Connectors/AP_ADO: J3.25; also elsewhere on the board
/Inputs_Connectors/DIO2: J3.27; also elsewhere on the board
/Inputs_Connectors/DIO23: J3.21; also elsewhere on the board
/Inputs_Connectors/FSYNC: J3.32; also elsewhere on the board
/Inputs_Connectors/INT1: J3.34; also elsewhere on the board
/Inputs_Connectors/INT2: J3.35; also elsewhere on the board
/Inputs_Connectors/R0_ANT_SW: J3.29; also elsewhere on the board
/Inputs_Connectors/R0_BUSY: J3.1; also elsewhere on the board
/Inputs_Connectors/R0_DIO1: J3.7; also elsewhere on the board
/Inputs_Connectors/R0_DIO3: J3.5; also elsewhere on the board
/Inputs_Connectors/R0_MISO: J3.13; also elsewhere on the board
/Inputs_Connectors/R0_MOSI: J3.11; also elsewhere on the board
/Inputs_Connectors/R0_NSS: J3.10; also elsewhere on the board
/Inputs_Connectors/R0_RST: J3.3; also elsewhere on the board
/Inputs_Connectors/R0_SCK: J3.9; also elsewhere on the board
/Inputs_Connectors/R1_ANT_SW: J3.19; also elsewhere on the board
/Inputs_Connectors/R1_BUSY: J3.15; also elsewhere on the board
/Inputs_Connectors/R1_DIO1: J3.12; also elsewhere on the board
/Inputs_Connectors/R1_DIO3: J3.16; also elsewhere on the board
/Inputs_Connectors/R1_MISO: J3.31; also elsewhere on the board
/Inputs_Connectors/R1_MOSI: J3.33; also elsewhere on the board
/Inputs_Connectors/R1_NSS: J3.37; also elsewhere on the board
/Inputs_Connectors/R1_RST: J3.17; also elsewhere on the board
/Inputs_Connectors/R1_SCK: J3.39; also elsewhere on the board
/Inputs_Connectors/SCL_SENS: J3.20; also elsewhere on the board
/Inputs_Connectors/SDA_SENS: J3.18; also elsewhere on the board
/Sensors/R0_DIO2: J3.8; also elsewhere on the board
/Sensors/R1_DIO2: J3.14; also elsewhere on the board
GND: J3.36, J3.38, J3.40; also elsewhere on the board
